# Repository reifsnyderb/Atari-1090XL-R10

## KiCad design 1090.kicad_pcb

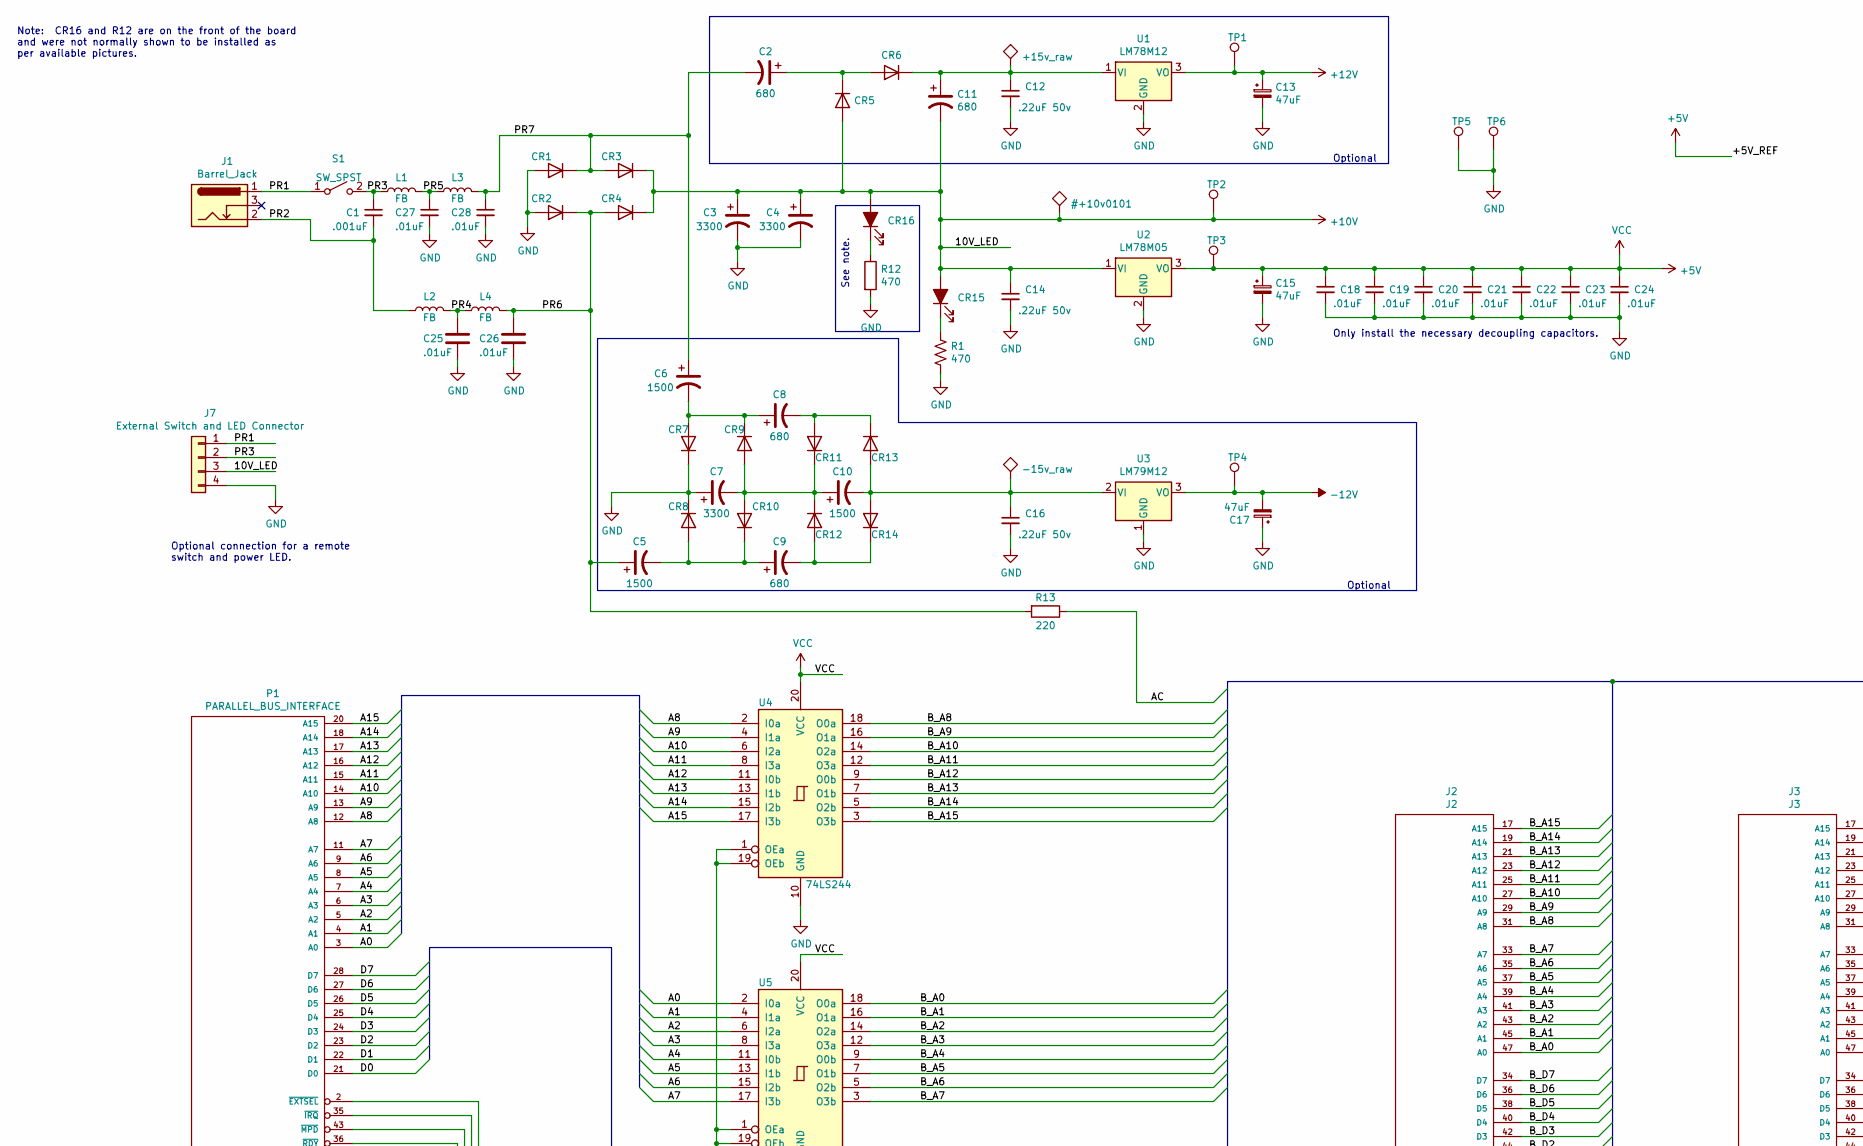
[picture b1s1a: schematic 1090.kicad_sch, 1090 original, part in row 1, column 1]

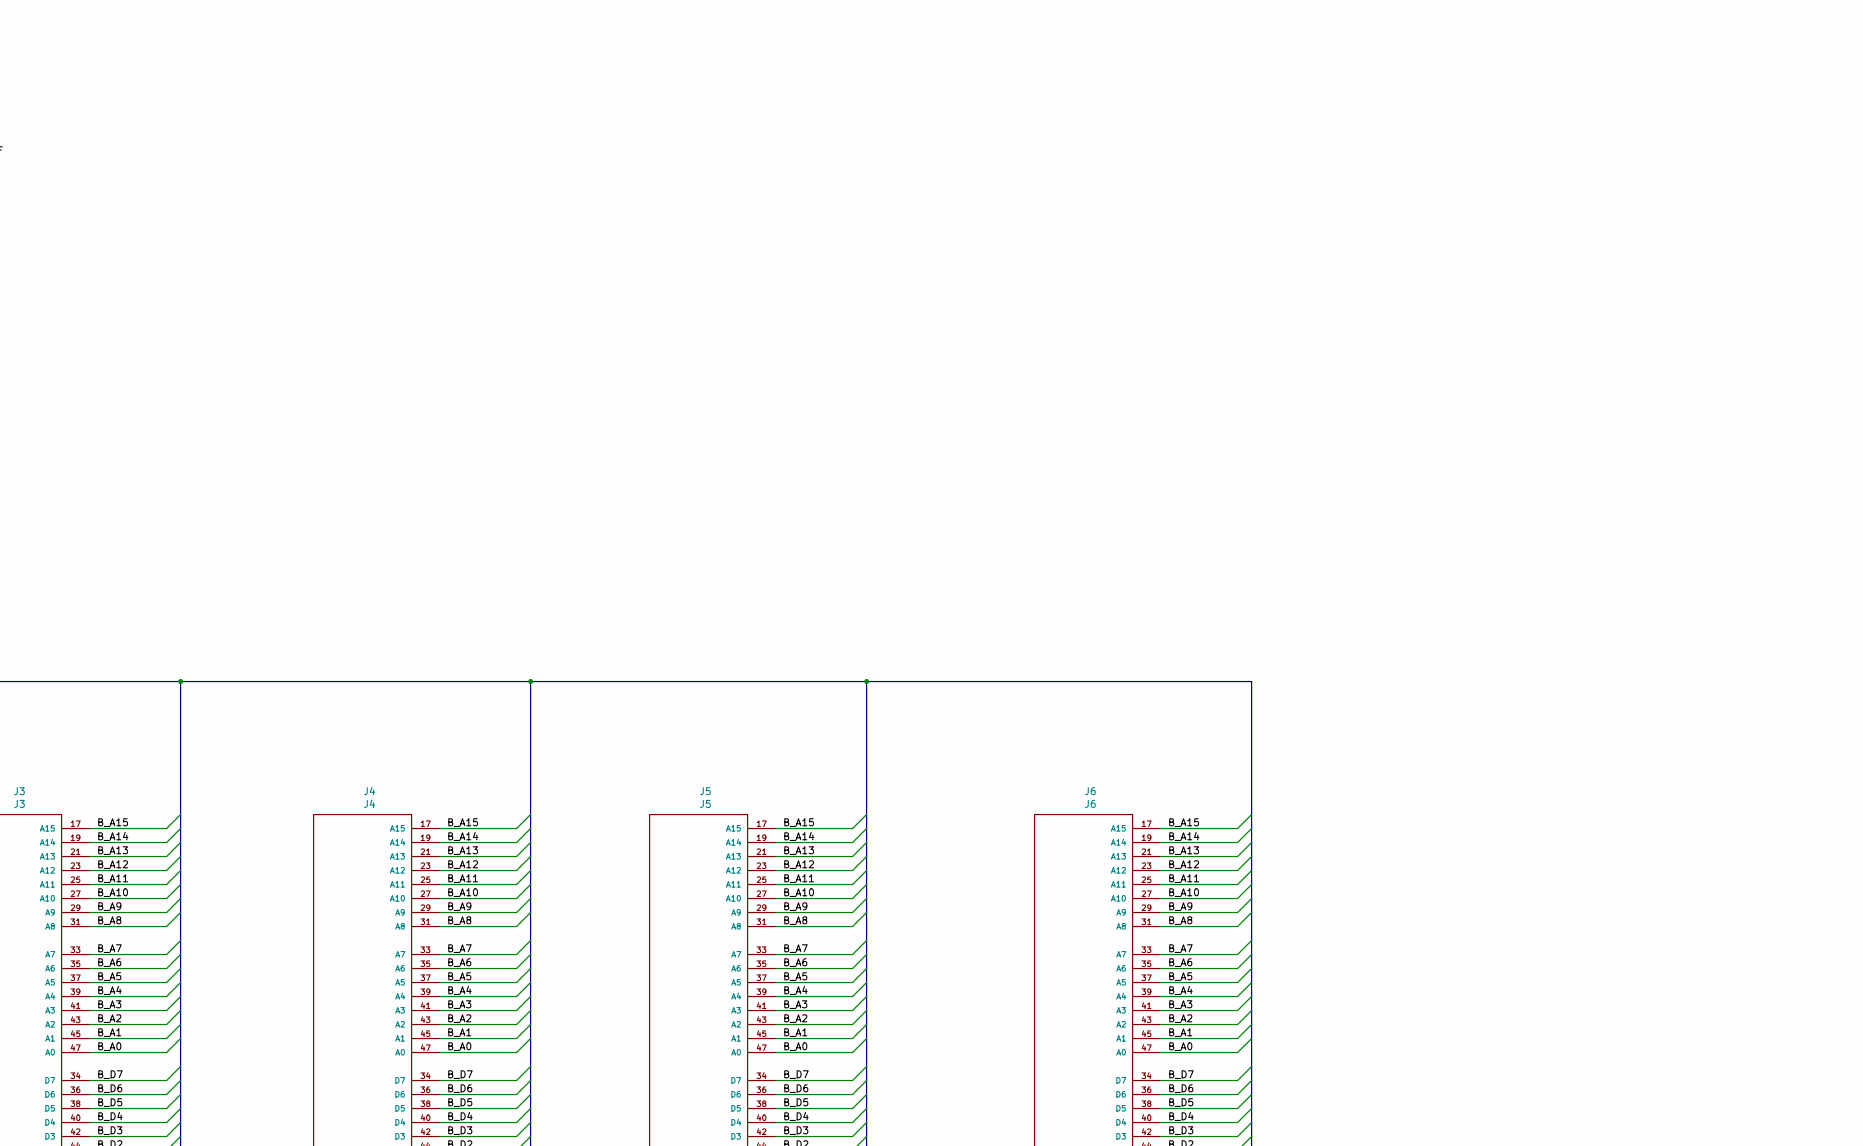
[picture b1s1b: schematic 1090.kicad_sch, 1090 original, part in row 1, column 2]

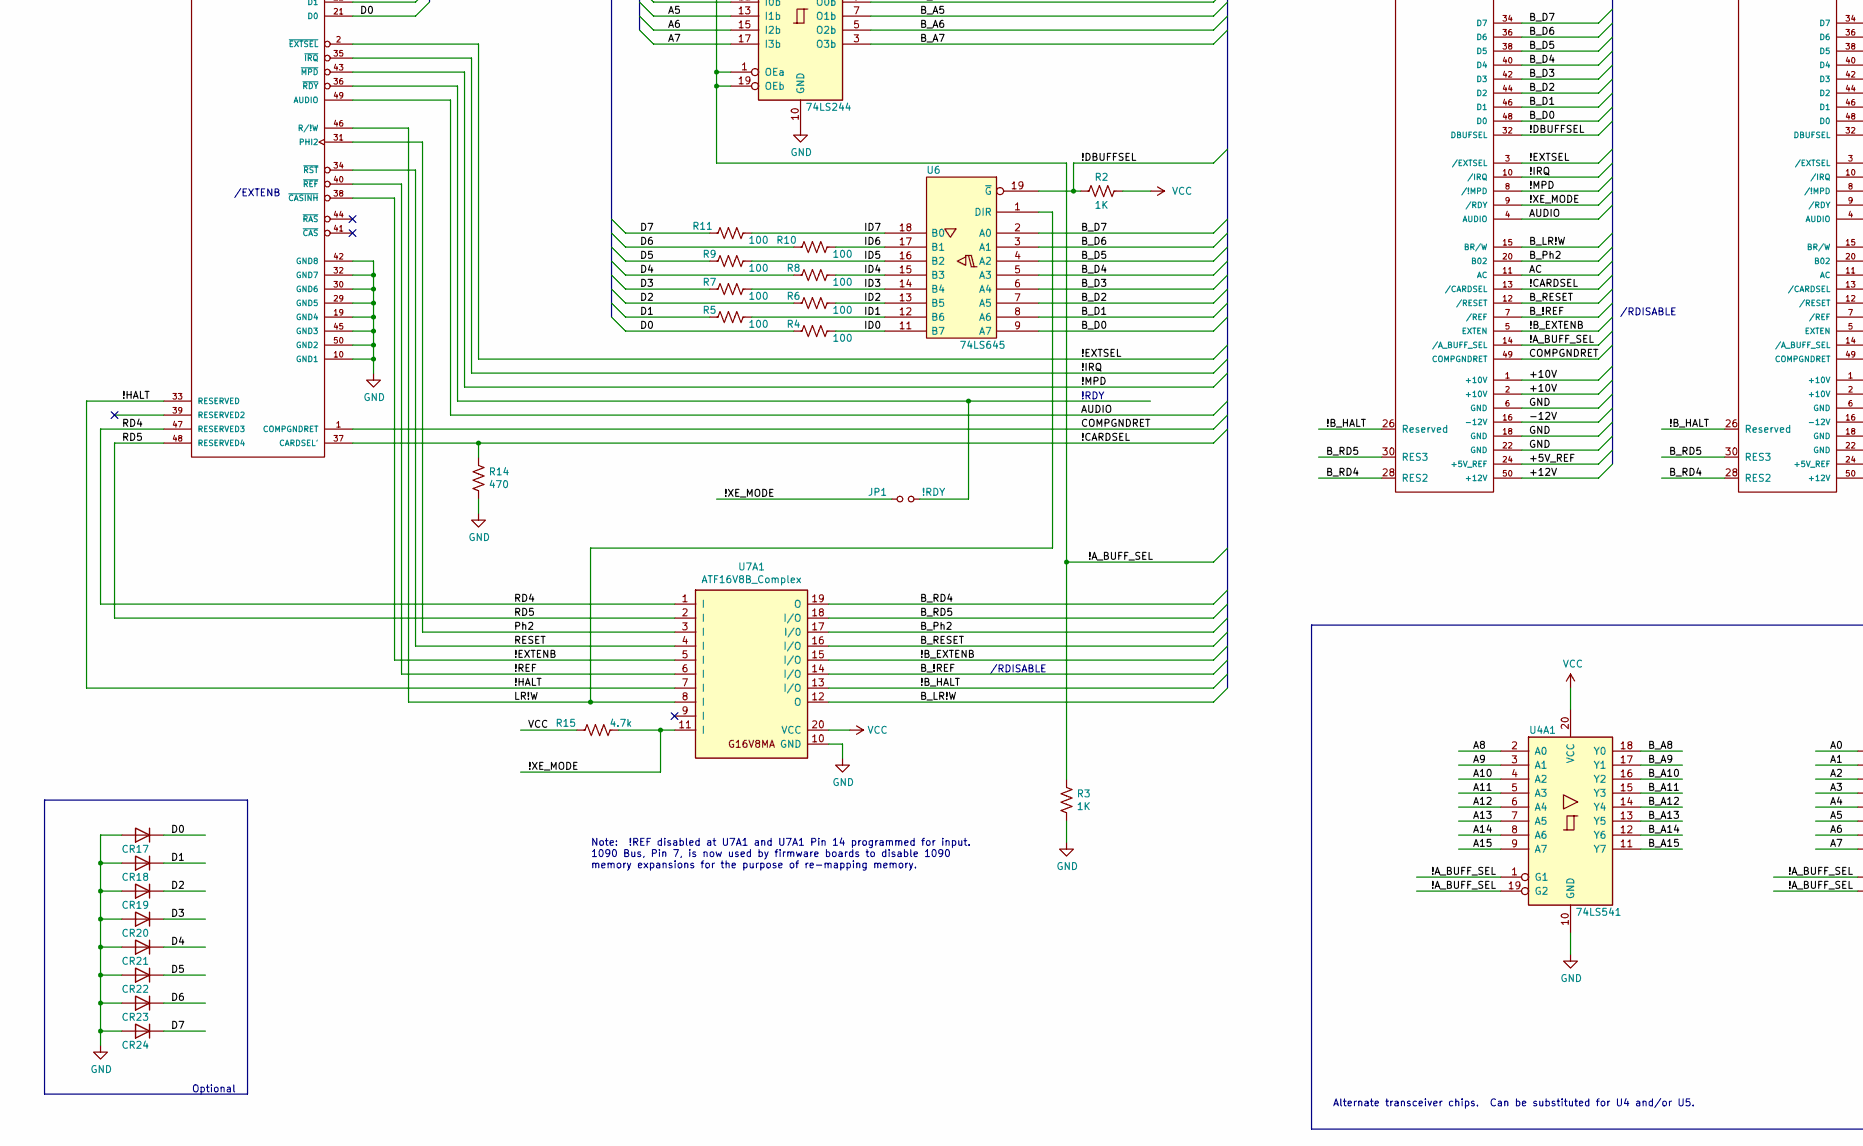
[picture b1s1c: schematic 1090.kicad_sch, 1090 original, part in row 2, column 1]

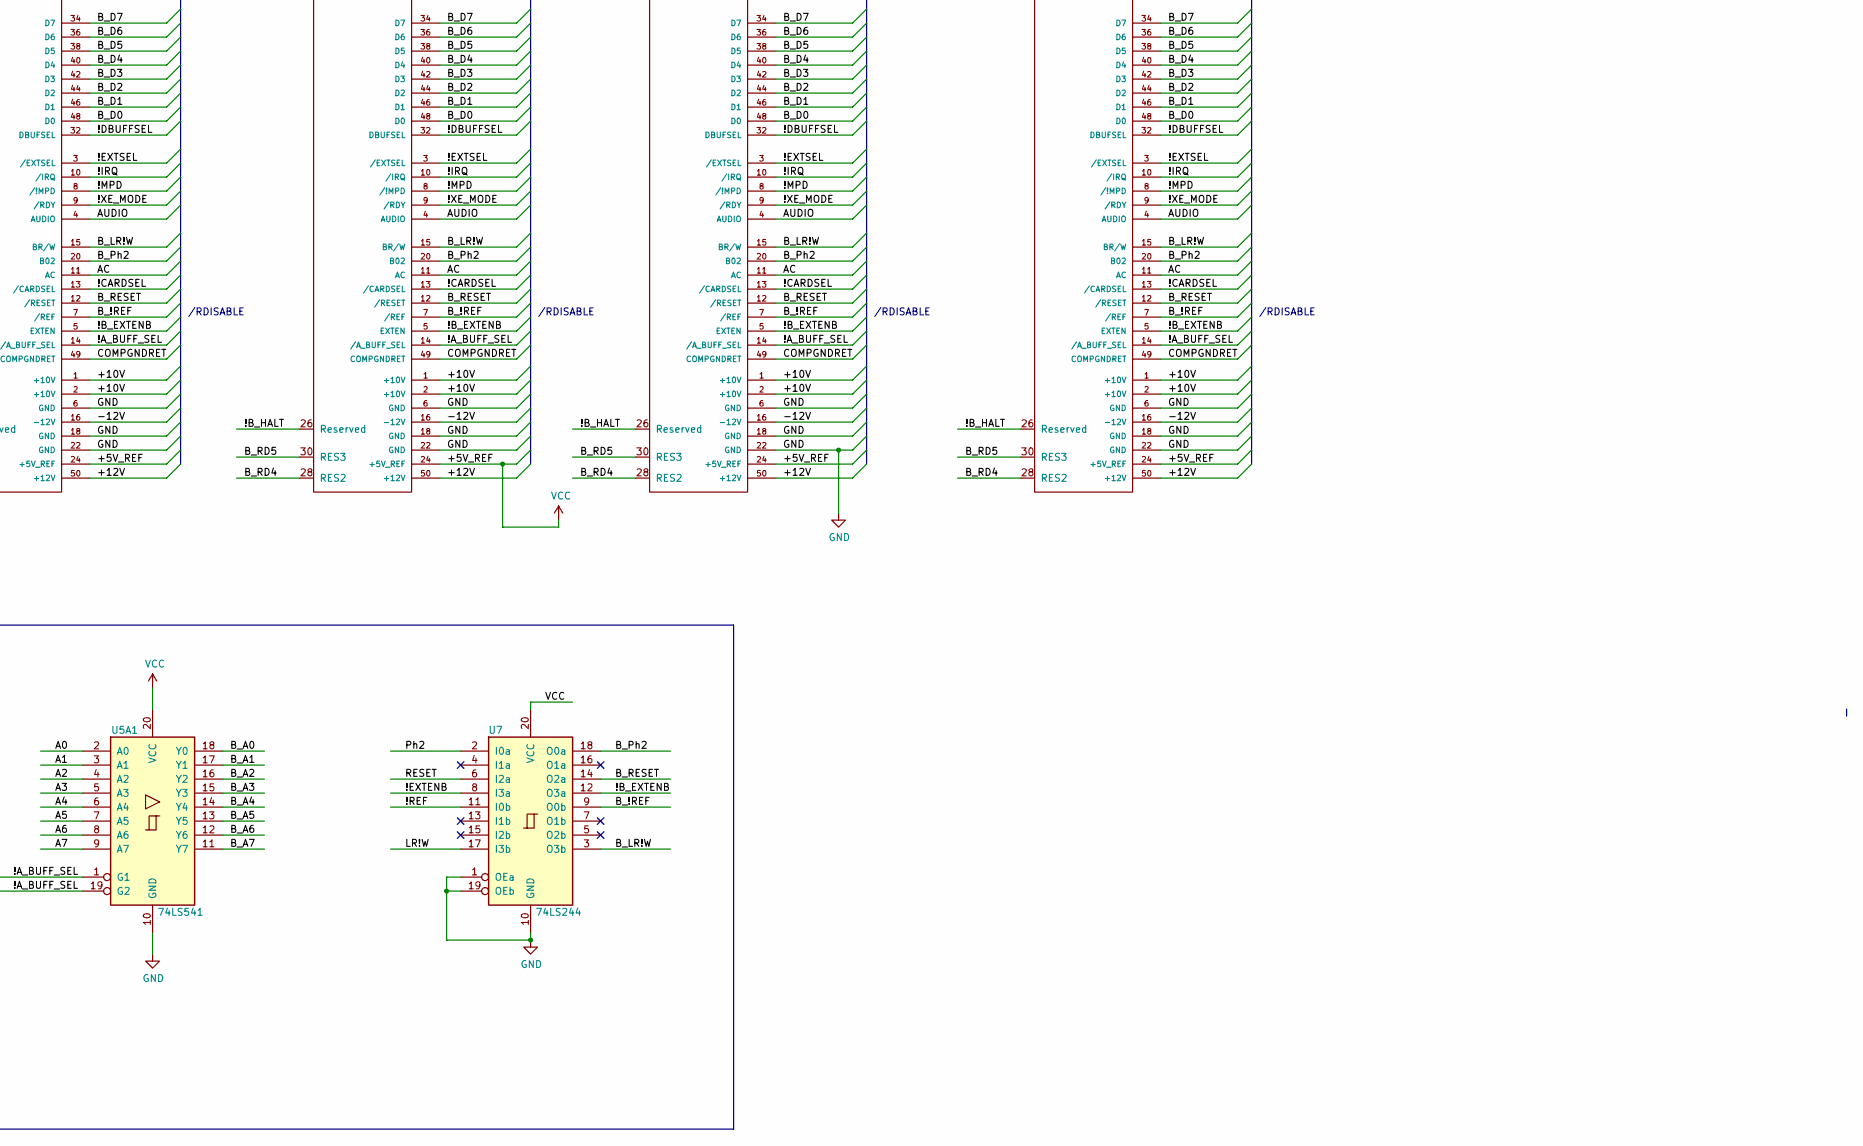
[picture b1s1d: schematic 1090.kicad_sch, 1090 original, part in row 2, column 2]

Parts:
C1: .001uF; C_Axial_L5.1mm_D3.1mm_P12.50mm_Horizontal
C2, C8, C9, C11: 680; CP_Radial_D12.5mm_P5.00mm
C3, C4, C7: 3300; CP_Radial_D22.0mm_P7.50_10.00mm_SnapIn
C5, C6: 1500; CP_Radial_D13.0mm_P7.50mm
C10: 1500; CP_Radial_D16.0mm_P7.50mm
C12, C14: .22uF 50v; C_Axial_L5.1mm_D3.1mm_P15.00mm_Horizontal
C13, C15, C17: 47uF; CP_Radial_D8.0mm_P2.50mm
C16: .22uF 50v; C_Axial_L5.1mm_D3.1mm_P12.50mm_Horizontal
C18, C19, C20, C21, C22, C23, C24, C25, C26, C27, C28: .01uF; C_Axial_L5.1mm_D3.1mm_P12.50mm_Horizontal
CR1, CR2, CR3, CR4: D; D_5KP_P10.16mm_Horizontal
CR5, CR6, CR7, CR8, CR9, CR10, CR11, CR12, CR13, CR14, CR17, CR18, CR19, CR20, CR21, CR22, CR23, CR24: D; D_Axial_L5.1mm_D3.1mm_P12.50mm_Horizontal
CR15, CR16: LED_ALT; LED_D5.0mm_FlatTop
J1: Barrel_Jack; BarrelJack_Wuerth_6941xx301002
J2: J2; AtariSocket_2x25_P2.54mm_Vertical
J3: J3; AtariSocket_2x25_P2.54mm_Vertical
J4: J4; AtariSocket_2x25_P2.54mm_Vertical
J5: J5; AtariSocket_2x25_P2.54mm_Vertical
J6: J6; AtariSocket_2x25_P2.54mm_Vertical
J7: External Switch and LED Connector; Molex_KK-396_A-41791-0004_1x04_P3.96mm_Vertical
JP1: !RDY; PinHeader_1x02_P2.54mm_Vertical
L1, L2, L3, L4: FB; L_Axial_L5.1mm_D3.1mm_P12.50mm_Horizontal
P1: PARALLEL_BUS_INTERFACE; Edge-50
R1, R12, R14: 470; R_Axial_L5.1mm_D3.1mm_P12.50mm_Horizontal
R2, R3: 1K; R_Axial_L5.1mm_D3.1mm_P12.50mm_Horizontal
R4, R5, R6, R7, R8, R9, R10, R11: 100; R_Axial_L5.1mm_D3.1mm_P12.50mm_Horizontal
R13: 220; R_Axial_L5.1mm_D3.1mm_P12.50mm_Horizontal
R15: 4.7k; R_Axial_L5.1mm_D3.1mm_P12.50mm_Horizontal
S1: SW_SPST; E101J1ABE2; Part # E101J1AQE2
TP1: +12V; Pin_D1.0mm_L10.0mm
TP2: +10V; Pin_D1.0mm_L10.0mm
TP3: TestPoint; Pin_D1.0mm_L10.0mm
TP4: -12V; Pin_D1.0mm_L10.0mm
TP5, TP6: GND; Pin_D1.0mm_L10.0mm
U1: LM78M12; TO-220-3_Vertical
U2: LM78M05; TO-220-3_Vertical
U3: LM79M12; TO-220-3_Vertical
U4, U5, U7: 74LS244; DIP-20_W7.62mm_Socket
U4A1, U5A1: 74LS541; DIP-20_W7.62mm_Socket
U6: 74LS645; DIP-20_W7.62mm_Socket
U7A1: ATF16V8B_Complex; DIP-20_W7.62mm_Socket

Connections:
+5V: C15.1, C18.1, C19.1, C20.1, C21.1, C22.1, C23.1, C24.1, J2.24 (+5V_REF), J3.24 (+5V_REF), J4.24 (+5V_REF), J5.24 (+5V_REF), J6.24 (+5V_REF), R2.1, R15.1, TP3.1, U2.3 (VO), U4.20 (VCC), U4A1.20 (VCC), U5.20 (VCC), U5A1.20 (VCC), U6.20 (VCC), U7.20 (VCC), U7A1.20 (VCC)
+10V: C3.1, C4.1, C11.2, C14.1, CR3.1 (K), CR4.1 (K), CR5.2 (A), CR15.2 (A), CR16.2 (A), J2.1 (+10V), J2.2 (+10V), J3.1 (+10V), J3.2 (+10V), J4.1 (+10V), J4.2 (+10V), J5.1 (+10V), J5.2 (+10V), J6.1 (+10V), J6.2 (+10V), J7.3, TP2.1, U2.1 (VI)
+12V: C13.1, J2.50 (+12V), J3.50 (+12V), J4.50 (+12V), J5.50 (+12V), J6.50 (+12V), TP1.1, U1.3 (VO)
-12V: C17.2, J2.16 (-12V), J3.16 (-12V), J4.16 (-12V), J5.16 (-12V), J6.16 (-12V), TP4.1, U3.3 (VO)
/!A_BUFF_SEL: J2.14 (/A_BUFF_SEL), J3.14 (/A_BUFF_SEL), J4.14 (/A_BUFF_SEL), J5.14 (/A_BUFF_SEL), J6.14 (/A_BUFF_SEL), R3.1, U4.1 (OEa), U4.19 (OEb), U4A1.1 (G1), U4A1.19 (G2), U5.1 (OEa), U5.19 (OEb), U5A1.1 (G1), U5A1.19 (G2)
/!B_EXTENB: J2.5 (EXTEN), J3.5 (EXTEN), J4.5 (EXTEN), J5.5 (EXTEN), J6.5 (EXTEN), U7.12 (O3a), U7A1.15 (I/O)
/!B_HALT: J2.26 (Reserved), J3.26 (Reserved), J4.26 (Reserved), J5.26 (Reserved), J6.26 (Reserved), U7A1.13 (I/O)
/!CARDSEL: J2.13 (/CARDSEL), J3.13 (/CARDSEL), J4.13 (/CARDSEL), J5.13 (/CARDSEL), J6.13 (/CARDSEL), P1.37 (CARDSEL'), R14.1
/!DBUFFSEL: J2.32 (DBUFSEL), J3.32 (DBUFSEL), J4.32 (DBUFSEL), J5.32 (DBUFSEL), J6.32 (DBUFSEL), R2.2, U6.19 (~G)
/!EXTENB: P1.38 (~CASINH), U7.8 (I3a), U7A1.5 (I)
/!EXTSEL: J2.3 (/EXTSEL), J3.3 (/EXTSEL), J4.3 (/EXTSEL), J5.3 (/EXTSEL), J6.3 (/EXTSEL), P1.2 (~EXTSEL)
/!HALT: P1.33 (RESERVED), U7A1.7 (I)
/!IRQ: J2.10 (/IRQ), J3.10 (/IRQ), J4.10 (/IRQ), J5.10 (/IRQ), J6.10 (/IRQ), P1.35 (~IRQ)
/!MPD: J2.8 (/!MPD), J3.8 (/!MPD), J4.8 (/!MPD), J5.8 (/!MPD), J6.8 (/!MPD), P1.43 (~MPD)
/!REF: P1.40 (~REF), U7.11 (I0b), U7A1.6 (I)
/!XE_MODE: J2.9 (/RDY), J3.9 (/RDY), J4.9 (/RDY), J5.9 (/RDY), J6.9 (/RDY), JP1.1, R15.2, U7A1.11 (I)
/A0: P1.3 (A0), U5.2 (I0a), U5A1.2 (A0)
/A1: P1.4 (A1), U5.4 (I1a), U5A1.3 (A1)
/A2: P1.5 (A2), U5.6 (I2a), U5A1.4 (A2)
/A3: P1.6 (A3), U5.8 (I3a), U5A1.5 (A3)
/A4: P1.7 (A4), U5.11 (I0b), U5A1.6 (A4)
/A5: P1.8 (A5), U5.13 (I1b), U5A1.7 (A5)
/A6: P1.9 (A6), U5.15 (I2b), U5A1.8 (A6)
/A7: P1.11 (A7), U5.17 (I3b), U5A1.9 (A7)
/A8: P1.12 (A8), U4.2 (I0a), U4A1.2 (A0)
/A9: P1.13 (A9), U4.4 (I1a), U4A1.3 (A1)
/A10: P1.14 (A10), U4.6 (I2a), U4A1.4 (A2)
/A11: P1.15 (A11), U4.8 (I3a), U4A1.5 (A3)
/A12: P1.16 (A12), U4.11 (I0b), U4A1.6 (A4)
/A13: P1.17 (A13), U4.13 (I1b), U4A1.7 (A5)
/A14: P1.18 (A14), U4.15 (I2b), U4A1.8 (A6)
/A15: P1.20 (A15), U4.17 (I3b), U4A1.9 (A7)
/AC: J2.11 (AC), J3.11 (AC), J4.11 (AC), J5.11 (AC), J6.11 (AC), R13.1
/AUDIO: J2.4 (AUDIO), J3.4 (AUDIO), J4.4 (AUDIO), J5.4 (AUDIO), J6.4 (AUDIO), P1.49 (AUDIO)
/B_!REF: J2.7 (/REF), J3.7 (/REF), J4.7 (/REF), J5.7 (/REF), J6.7 (/REF), U7.9 (O0b), U7A1.14 (I/O)
/B_A0: J2.47 (A0), J3.47 (A0), J4.47 (A0), J5.47 (A0), J6.47 (A0), U5.18 (O0a), U5A1.18 (Y0)
/B_A1: J2.45 (A1), J3.45 (A1), J4.45 (A1), J5.45 (A1), J6.45 (A1), U5.16 (O1a), U5A1.17 (Y1)
/B_A2: J2.43 (A2), J3.43 (A2), J4.43 (A2), J5.43 (A2), J6.43 (A2), U5.14 (O2a), U5A1.16 (Y2)
/B_A3: J2.41 (A3), J3.41 (A3), J4.41 (A3), J5.41 (A3), J6.41 (A3), U5.12 (O3a), U5A1.15 (Y3)
/B_A4: J2.39 (A4), J3.39 (A4), J4.39 (A4), J5.39 (A4), J6.39 (A4), U5.9 (O0b), U5A1.14 (Y4)
/B_A5: J2.37 (A5), J3.37 (A5), J4.37 (A5), J5.37 (A5), J6.37 (A5), U5.7 (O1b), U5A1.13 (Y5)
/B_A6: J2.35 (A6), J3.35 (A6), J4.35 (A6), J5.35 (A6), J6.35 (A6), U5.5 (O2b), U5A1.12 (Y6)
/B_A7: J2.33 (A7), J3.33 (A7), J4.33 (A7), J5.33 (A7), J6.33 (A7), U5.3 (O3b), U5A1.11 (Y7)
/B_A8: J2.31 (A8), J3.31 (A8), J4.31 (A8), J5.31 (A8), J6.31 (A8), U4.18 (O0a), U4A1.18 (Y0)
/B_A9: J2.29 (A9), J3.29 (A9), J4.29 (A9), J5.29 (A9), J6.29 (A9), U4.16 (O1a), U4A1.17 (Y1)
/B_A10: J2.27 (A10), J3.27 (A10), J4.27 (A10), J5.27 (A10), J6.27 (A10), U4.14 (O2a), U4A1.16 (Y2)
/B_A11: J2.25 (A11), J3.25 (A11), J4.25 (A11), J5.25 (A11), J6.25 (A11), U4.12 (O3a), U4A1.15 (Y3)
/B_A12: J2.23 (A12), J3.23 (A12), J4.23 (A12), J5.23 (A12), J6.23 (A12), U4.9 (O0b), U4A1.14 (Y4)
/B_A13: J2.21 (A13), J3.21 (A13), J4.21 (A13), J5.21 (A13), J6.21 (A13), U4.7 (O1b), U4A1.13 (Y5)
/B_A14: J2.19 (A14), J3.19 (A14), J4.19 (A14), J5.19 (A14), J6.19 (A14), U4.5 (O2b), U4A1.12 (Y6)
/B_A15: J2.17 (A15), J3.17 (A15), J4.17 (A15), J5.17 (A15), J6.17 (A15), U4.3 (O3b), U4A1.11 (Y7)
/B_D0: J2.48 (D0), J3.48 (D0), J4.48 (D0), J5.48 (D0), J6.48 (D0), U6.9 (A7)
/B_D1: J2.46 (D1), J3.46 (D1), J4.46 (D1), J5.46 (D1), J6.46 (D1), U6.8 (A6)
/B_D2: J2.44 (D2), J3.44 (D2), J4.44 (D2), J5.44 (D2), J6.44 (D2), U6.7 (A5)
/B_D3: J2.42 (D3), J3.42 (D3), J4.42 (D3), J5.42 (D3), J6.42 (D3), U6.6 (A4)
/B_D4: J2.40 (D4), J3.40 (D4), J4.40 (D4), J5.40 (D4), J6.40 (D4), U6.5 (A3)
/B_D5: J2.38 (D5), J3.38 (D5), J4.38 (D5), J5.38 (D5), J6.38 (D5), U6.4 (A2)
/B_D6: J2.36 (D6), J3.36 (D6), J4.36 (D6), J5.36 (D6), J6.36 (D6), U6.3 (A1)
/B_D7: J2.34 (D7), J3.34 (D7), J4.34 (D7), J5.34 (D7), J6.34 (D7), U6.2 (A0)
/B_LR!W: J2.15 (BR/W), J3.15 (BR/W), J4.15 (BR/W), J5.15 (BR/W), J6.15 (BR/W), U7.3 (O3b), U7A1.12 (O)
/B_Ph2: J2.20 (B02), J3.20 (B02), J4.20 (B02), J5.20 (B02), J6.20 (B02), U7.18 (O0a), U7A1.17 (I/0)
/B_RD4: J2.28 (RES2), J3.28 (RES2), J4.28 (RES2), J5.28 (RES2), J6.28 (RES2), U7A1.19 (O)
/B_RD5: J2.30 (RES3), J3.30 (RES3), J4.30 (RES3), J5.30 (RES3), J6.30 (RES3), U7A1.18 (I/O)
/B_RESET: J2.12 (/RESET), J3.12 (/RESET), J4.12 (/RESET), J5.12 (/RESET), J6.12 (/RESET), U7.14 (O2a), U7A1.16 (I/O)
/COMPGNDRET: J2.49 (COMPGNDRET), J3.49 (COMPGNDRET), J4.49 (COMPGNDRET), J5.49 (COMPGNDRET), J6.49 (COMPGNDRET), P1.1 (COMPGNDRET)
/D0: CR17.1 (K), P1.21 (D0), R4.2
/D1: CR18.1 (K), P1.22 (D1), R5.2
/D2: CR19.1 (K), P1.23 (D2), R6.2
/D3: CR20.1 (K), P1.24 (D3), R7.2
/D4: CR21.1 (K), P1.25 (D4), R8.2
/D5: CR22.1 (K), P1.26 (D5), R9.2
/D6: CR23.1 (K), P1.27 (D6), R10.2
/D7: CR24.1 (K), P1.28 (D7), R11.2
/ID0: R4.1, U6.11 (B7)
/ID1: R5.1, U6.12 (B6)
/ID2: R6.1, U6.13 (B5)
/ID3: R7.1, U6.14 (B4)
/ID4: R8.1, U6.15 (B3)
/ID5: R9.1, U6.16 (B2)
/ID6: R10.1, U6.17 (B1)
/ID7: R11.1, U6.18 (B0)
/LR!W: P1.46 (R/!W), U6.1 (DIR), U7.17 (I3b), U7A1.8 (I)
/PR1: J1.1, J7.1, S1.1 (A)
/PR2: C1.2, J1.2, L2.1
/PR3: C1.1, J7.2, L1.1, S1.2 (B)
/PR4: C25.1, L2.2, L4.1
/PR5: C27.1, L1.2, L3.1
/PR6: C5.1, C26.1, CR2.1 (K), CR4.2 (A), L4.2, R13.2
/PR7: C2.2, C6.1, C28.1, CR1.1 (K), CR3.2 (A), L3.2
/Ph2: P1.31 (PHI2), U7.2 (I0a), U7A1.3 (I)
/RD4: P1.47 (RESERVED3), U7A1.1 (I)
/RD5: P1.48 (RESERVED4), U7A1.2 (I)
/RESET: P1.34 (~RST), U7.6 (I2a), U7A1.4 (I)
GND: C3.2, C4.2, C7.1, C12.2, C13.2, C14.2, C15.2, C16.2, C17.1, C18.2, C19.2, C20.2, C21.2, C22.2, C23.2, C24.2, C25.2, C26.2, C27.2, C28.2, CR1.2 (A), CR2.2 (A), CR7.1 (K), CR8.1 (K), CR17.2 (A), CR18.2 (A), CR19.2 (A), CR20.2 (A), CR21.2 (A), CR22.2 (A), CR23.2 (A), CR24.2 (A), J2.6 (GND), J2.18 (GND), J2.22 (GND), J3.6 (GND), J3.18 (GND), J3.22 (GND), J4.6 (GND), J4.18 (GND), J4.22 (GND), J5.6 (GND), J5.18 (GND), J5.22 (GND), J6.6 (GND), J6.18 (GND), J6.22 (GND), J7.4, P1.10 (GND1), P1.19 (GND4), P1.29 (GND5), P1.30 (GND6), P1.32 (GND7), P1.42 (GND8), P1.45 (GND3), P1.50 (GND2), R1.2, R3.2, R12.2, R14.2, TP5.1, TP6.1, U1.2 (GND), U2.2 (GND), U3.1 (GND), U4.10 (GND), U4A1.10 (GND), U5.10 (GND), U5A1.10 (GND), U6.10 (GND), U7.1 (OEa), U7.10 (GND), U7.19 (OEb), U7A1.10 (GND)
unnamed: C2.1, CR5.1 (K), CR6.2 (A)
unnamed: C5.2, C9.1, CR8.2 (A), CR10.1 (K)
unnamed: C6.2, C8.1, CR7.2 (A), CR9.1 (K)
unnamed: C8.2, CR11.2 (A), CR13.1 (K)
unnamed: C9.2, CR12.2 (A), CR14.1 (K)
unnamed: C7.2, C10.1, CR9.2 (A), CR10.2 (A), CR11.1 (K), CR12.1 (K)
unnamed: C10.2, C16.1, CR13.2 (A), CR14.2 (A), U3.2 (VI)
unnamed: C11.1, C12.1, CR6.1 (K), U1.1 (VI)
unnamed: CR15.1 (K), R1.1
unnamed: CR16.1 (K), R12.1
unnamed: JP1.2, P1.36 (~RDY)

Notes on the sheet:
Optional
/RDISABLE
Note: CR16 and R12 are on the front of the board and were not normally shown to be installed as per available pictures.
!RDY
Note: !REF disabled at U7A1 and U7A1 Pin 14 programmed for input. 1090 Bus, Pin 7, is now used by firmware boards to disable 1090 memory expansions for the purpose of re-mapping memory.
Only install the necessary decoupling capacitors.
Optional connection for a remote switch and power LED.
/EXTENB
Alternate transceiver chips. Can be substituted for U4 and/or U5.
See note.

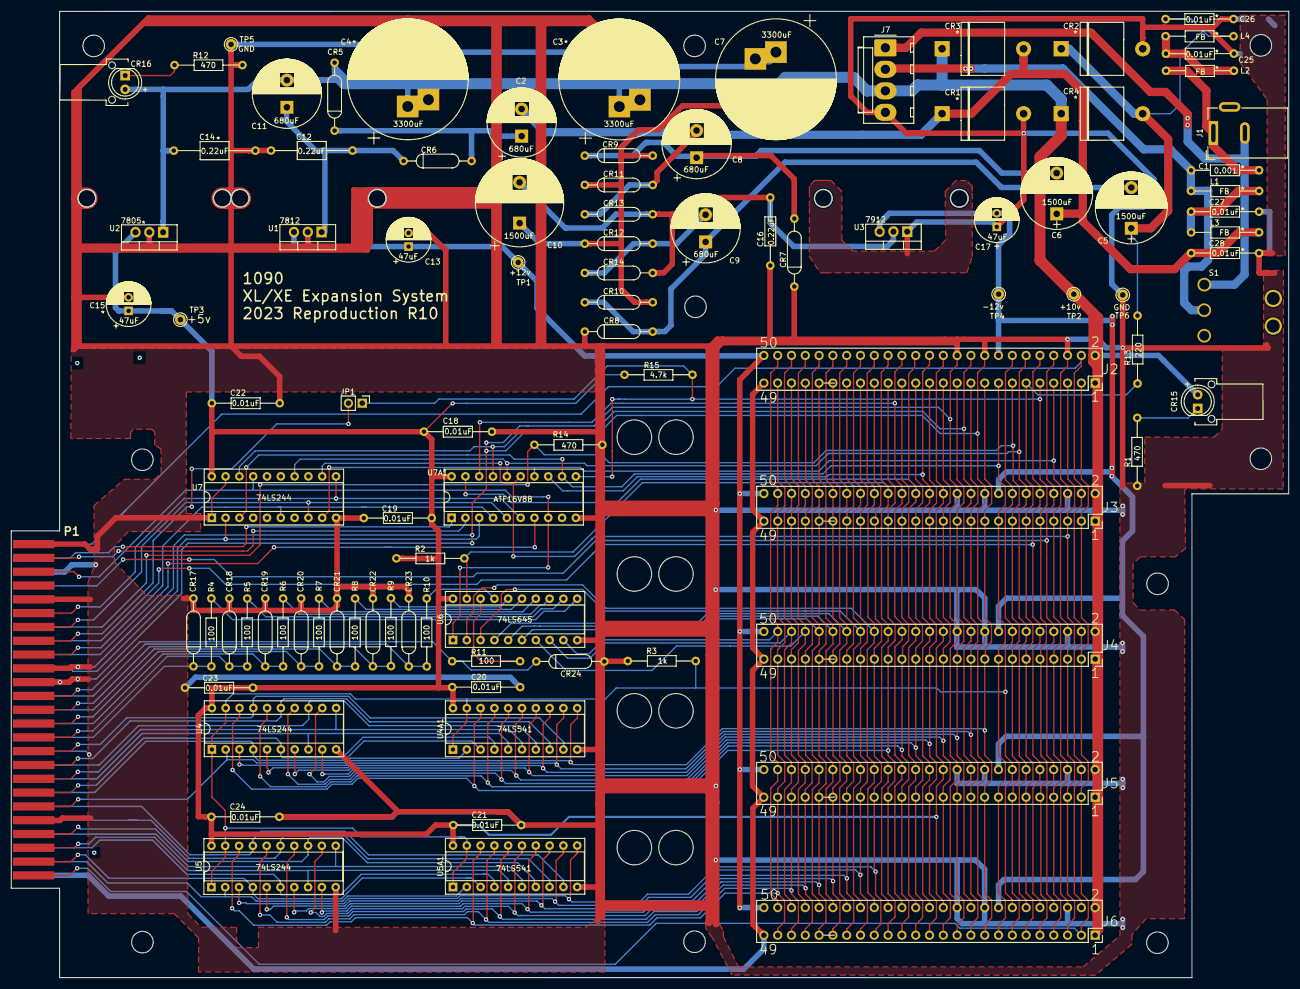
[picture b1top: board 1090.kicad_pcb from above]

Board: 2 copper layers, 235.1 x 177.8 mm, 97 parts (1 on the bottom side), 105 nets.

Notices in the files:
parts and their libraries:
Copyright 2021 Accelerated Designs. All rights reserved.
